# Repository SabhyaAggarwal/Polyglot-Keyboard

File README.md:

# Polyglot-Keyboard
This is a keyboard made by me that can change between stenography mode and QWERTY mode. It is basically a cheaper version of the [Polyglot Keyboard by Steno Keyboards](https://stenokeyboards.com/products/polyglot-keyboard). It uses the QMK Firmware. The PCB was made in KiCad. The case was designed in OnShape. It is quite effective and also very beautiful. The design and shape are customised for my personal use...

## BOM

|Name                 |Description                                                                                 |Quantity|Total Cost|Link                                                                                                                               |Distributor|
|---------------------|--------------------------------------------------------------------------------------------|--------|----------|-----------------------------------------------------------------------------------------------------------------------------------|-----------|
|PCB                  |Main PCB(includes payment fee)                                                              |1       |$1.36     |https://aivon.com/                                                                                                                 |AIVON      |
|RP2040 Zero          |Main Dev Board(cost includes shipping)                                                      |1       |$4.73     |https://robu.in/product/waveshare-rp2040-zero-without-header/                                                                      |robu       |
|MX Switches          |MX switches(pack of 10 and 4 of them = 40 keys and rest 2 keys given by another HackClubber)|4       |$2.86     |https://meckeys.com/shop/accessories/keyboard-accessories/key-switches/regular-switch-3pin/?attribute_pa_key-switches=regular-black|meckeys    |
|Keycaps              |Blank Keycaps(pack of 5)                                                                    |9       |$8.58     |https://meckeys.com/shop/accessories/keyboard-accessories/keycaps/blank/blank-dsa-keycaps-1u/?attribute_pa_variations=black        |meckeys    |
|1N4148 Diode         |1N4148 Diode(price not include shipping as shipping is shared with the RP2040 Zero)         |42      |$0.55     |https://robu.in/product/1n4148-1w-zener-diode-pack-of-50/                                                                          |robu       |
|M3x3mm Heatset Insert|M3 X 3mm Brass Threaded Inserts(includes shipping cost)                                     |3       |$0.94     |https://onlyscrews.in/products/m3-x-3mm-brass-threaded-inserts?variant=49729062273337                                              |onlyscrews |
|M3x5mm Screws        |Screws(shipping grouped with inserts)                                                       |3       |$0.06     |https://onlyscrews.in/products/m3-x-5mm-phillips-pan-head-ss-304-screw-dia-3mm-length-5mm?variant=50614141059385                   |onlyscrews |

## Images

### Keymap in Stenography mode

### Keymap in QWERTY mode

### 3D Render of the  assembled keyboard

### Case

#### Note: You can find the OnShape link [here](https://cad.onshape.com/documents/46c4256cf36649b9a784f734/w/7d5e5e40fb0c8f37601f916c/e/410489c67a58600f0a7678ff?renderMode=0&uiState=6a6b428066cc2ba4694d229c)...

### PCB Schematic

### PCB Design

### PCB 3D Render

.png)

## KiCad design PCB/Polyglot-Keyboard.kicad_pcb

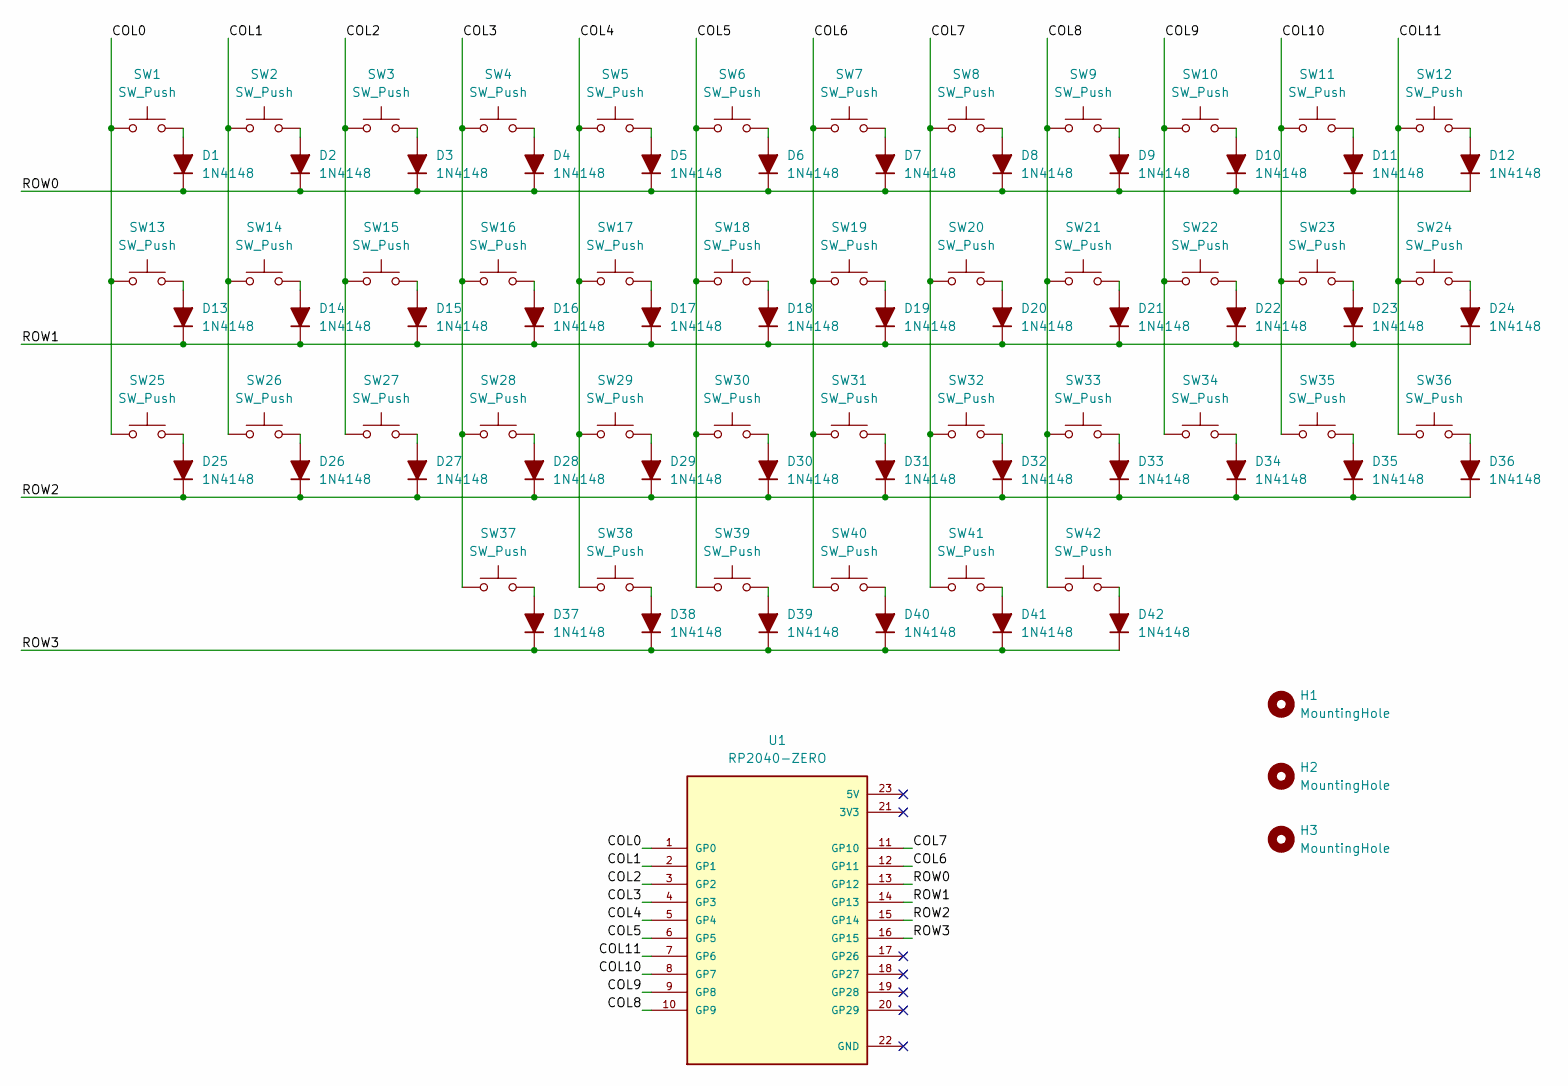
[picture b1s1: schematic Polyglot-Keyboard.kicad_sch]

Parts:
D1, D2, D3, D4, D5, D6, D7, D8, D9, D10, D11, D12, D13, D14, D15, D16, D17, D18, D19, D20, D21, D22, D23, D24, D25, D26, D27, D28, D29, D30, D31, D32, D33, D34, D35, D36, D37, D38, D39, D40, D41, D42: 1N4148; D_DO-35_SOD27_P7.62mm_Horizontal
H1, H2, H3: MountingHole; MountingHole_3.2mm_M3
SW1, SW2, SW3, SW4, SW5, SW6, SW7, SW8, SW9, SW10, SW11, SW12, SW13, SW14, SW15, SW16, SW17, SW18, SW19, SW20, SW21, SW22, SW23, SW24, SW25, SW26, SW27, SW28, SW29, SW30, SW31, SW32, SW33, SW34, SW35, SW36, SW37, SW38, SW39, SW40, SW41, SW42: SW_Push; SW_MX_1u
U1: RP2040-ZERO; MODULE_RP2040-ZERO; PARTREV NA

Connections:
/COL0: SW1.1, SW13.1, SW25.1, U1.1 (GP0)
/COL1: SW2.1, SW14.1, SW26.1, U1.2 (GP1)
/COL2: SW3.1, SW15.1, SW27.1, U1.3 (GP2)
/COL3: SW4.1, SW16.1, SW28.1, SW37.1, U1.4 (GP3)
/COL4: SW5.1, SW17.1, SW29.1, SW38.1, U1.5 (GP4)
/COL5: SW6.1, SW18.1, SW30.1, SW39.1, U1.6 (GP5)
/COL6: SW7.1, SW19.1, SW31.1, SW40.1, U1.12 (GP11)
/COL7: SW8.1, SW20.1, SW32.1, SW41.1, U1.11 (GP10)
/COL8: SW9.1, SW21.1, SW33.1, SW42.1, U1.10 (GP9)
/COL9: SW10.1, SW22.1, SW34.1, U1.9 (GP8)
/COL10: SW11.1, SW23.1, SW35.1, U1.8 (GP7)
/COL11: SW12.1, SW24.1, SW36.1, U1.7 (GP6)
/ROW0: D1.1 (K), D2.1 (K), D3.1 (K), D4.1 (K), D5.1 (K), D6.1 (K), D7.1 (K), D8.1 (K), D9.1 (K), D10.1 (K), D11.1 (K), D12.1 (K), U1.13 (GP12)
/ROW1: D13.1 (K), D14.1 (K), D15.1 (K), D16.1 (K), D17.1 (K), D18.1 (K), D19.1 (K), D20.1 (K), D21.1 (K), D22.1 (K), D23.1 (K), D24.1 (K), U1.14 (GP13)
/ROW2: D25.1 (K), D26.1 (K), D27.1 (K), D28.1 (K), D29.1 (K), D30.1 (K), D31.1 (K), D32.1 (K), D33.1 (K), D34.1 (K), D35.1 (K), D36.1 (K), U1.15 (GP14)
/ROW3: D37.1 (K), D38.1 (K), D39.1 (K), D40.1 (K), D41.1 (K), D42.1 (K), U1.16 (GP15)
unnamed: D1.2 (A), SW1.2
unnamed: D2.2 (A), SW2.2
unnamed: D3.2 (A), SW3.2
unnamed: D4.2 (A), SW4.2
unnamed: D5.2 (A), SW5.2
unnamed: D6.2 (A), SW6.2
unnamed: D7.2 (A), SW7.2
unnamed: D8.2 (A), SW8.2
unnamed: D9.2 (A), SW9.2
unnamed: D10.2 (A), SW10.2
unnamed: D11.2 (A), SW11.2
unnamed: D12.2 (A), SW12.2
unnamed: D13.2 (A), SW13.2
unnamed: D14.2 (A), SW14.2
unnamed: D15.2 (A), SW15.2
unnamed: D16.2 (A), SW16.2
unnamed: D17.2 (A), SW17.2
unnamed: D18.2 (A), SW18.2
unnamed: D19.2 (A), SW19.2
unnamed: D20.2 (A), SW20.2
unnamed: D21.2 (A), SW21.2
unnamed: D22.2 (A), SW22.2
unnamed: D23.2 (A), SW23.2
unnamed: D24.2 (A), SW24.2
unnamed: D25.2 (A), SW25.2
unnamed: D26.2 (A), SW26.2
unnamed: D27.2 (A), SW27.2
unnamed: D28.2 (A), SW28.2
unnamed: D29.2 (A), SW29.2
unnamed: D30.2 (A), SW30.2
unnamed: D31.2 (A), SW31.2
unnamed: D32.2 (A), SW32.2
unnamed: D33.2 (A), SW33.2
unnamed: D34.2 (A), SW34.2
unnamed: D35.2 (A), SW35.2
unnamed: D36.2 (A), SW36.2
unnamed: D37.2 (A), SW37.2
unnamed: D38.2 (A), SW38.2
unnamed: D39.2 (A), SW39.2
unnamed: D40.2 (A), SW40.2
unnamed: D41.2 (A), SW41.2
unnamed: D42.2 (A), SW42.2

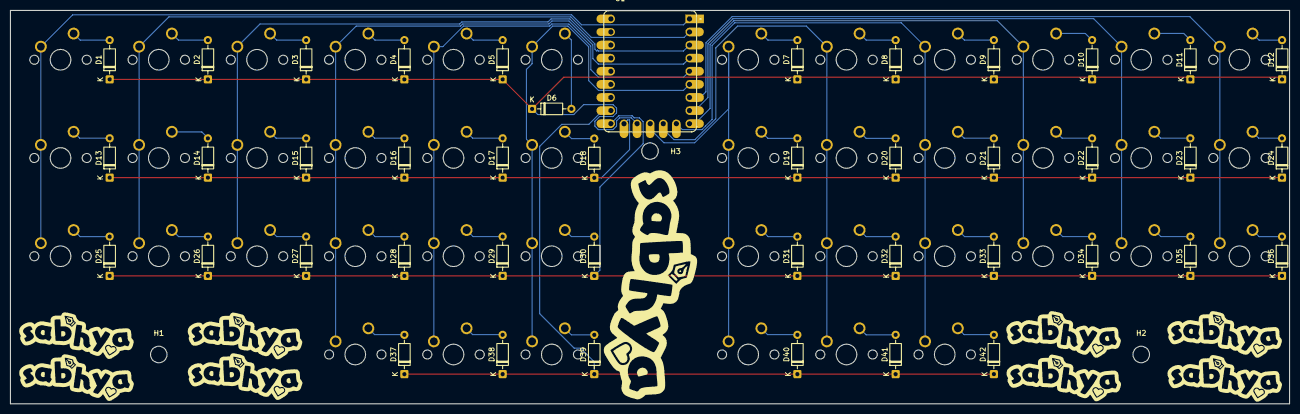
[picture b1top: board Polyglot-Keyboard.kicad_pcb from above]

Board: 2 copper layers, 248.0 x 76.3 mm, 88 parts (0 on the bottom side), 58 nets.

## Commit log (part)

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2026-06-24 Initialize JOURNAL.md with header
2026-06-24 Add PCB files and create first journal
2026-06-24 Add some images
2026-06-24 Revise journal entries for June 24 tasks
    Updated journal entries to reflect schematic and PCB work done on June 24, including time spent on each task.
2026-06-25 Add case files and fix PCB
2026-06-25 Add Firmware
2026-06-25 Add keymap images
2026-06-25 Syncing
2026-06-25 Add BOM.csv to PRODUCTION folder
2026-06-30 Add BOM.csv to root folder
